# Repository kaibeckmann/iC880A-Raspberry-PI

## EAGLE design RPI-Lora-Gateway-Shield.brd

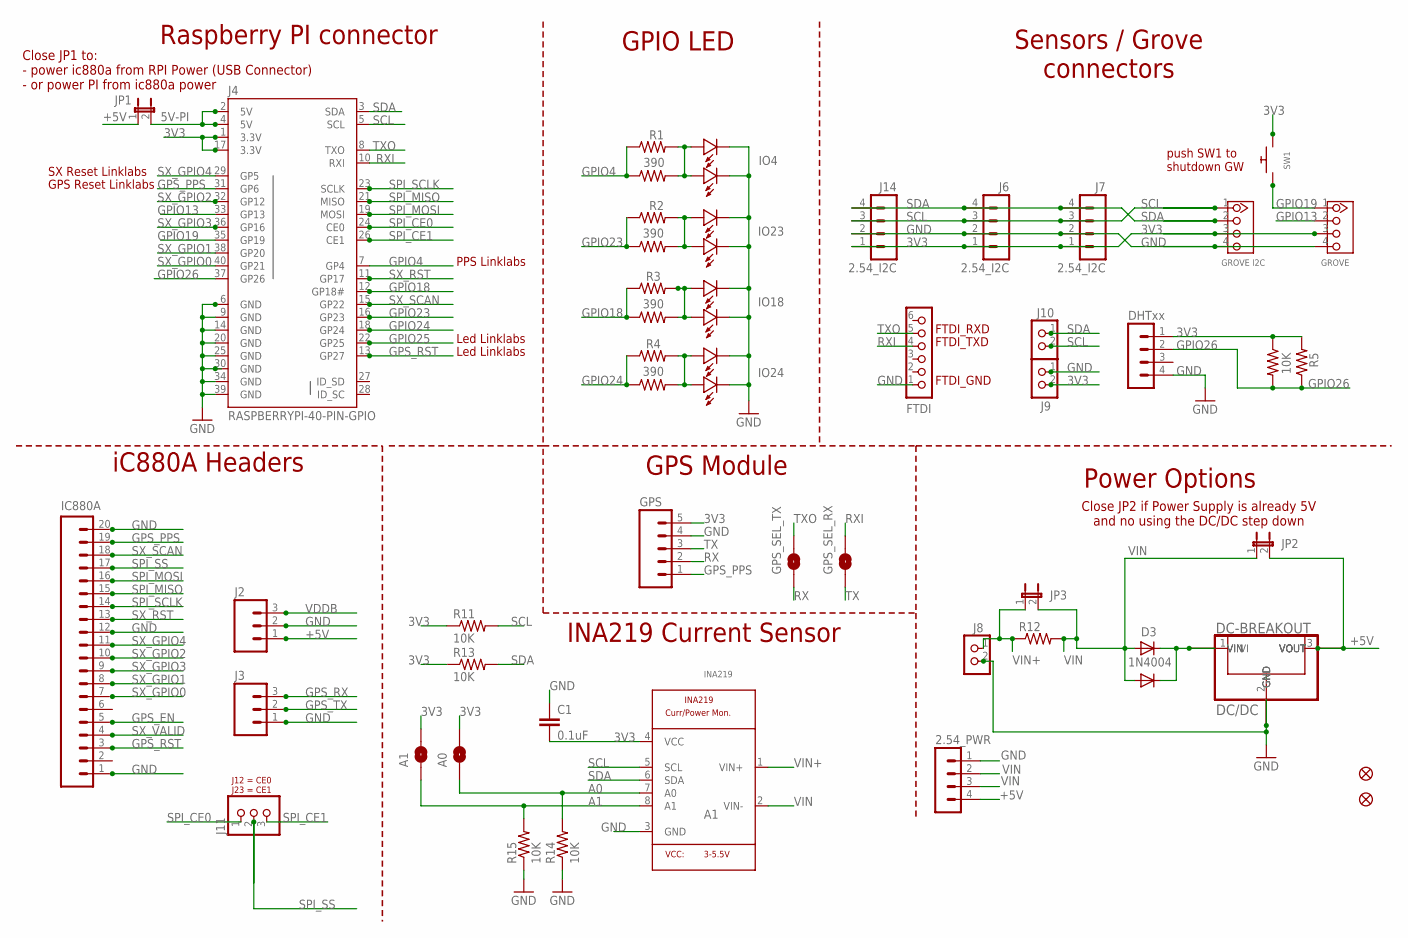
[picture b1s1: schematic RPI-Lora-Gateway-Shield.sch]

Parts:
A0, A1: SOLDERJUMPERNO; SJ_2S-NO
C1: 0.1uF; 0805-CAP
D3: 1N4004; DO41-10
D4: 1N4007; DO-214AC
DC/DC: DC-BREAKOUT
FID2, FID3: FIDUCIAL""; FIDUCIAL_1MM
FTDI: CON_HEADER_1X06-PTH; M1X6
GPS: M05PTH; 1X05
GPS_SEL_RX: SOLDERJUMPERNO; SJ_2S-NO
GPS_SEL_TX: SOLDERJUMPERNO; SJ_2S-NO
IC880A: M20LOCK; 1X20_LOCK
INA219: INA219; SOT23-8
J1: GROVE; HW4-2.0
J2, J3: M03LOCK; 1X03_LOCK
J4: RASPBERRYPI-40-PIN-GPIO; 2X20-SHROUDED
J5: DHTxx; 1X04_NO_LOCK
J6, J7, J14: 2.54_I2C; 1X04_NO_LOCK
J8, J9, J10: CON_TERMINAL_BLOCK_02-5MM; TERMINAL_BLOCK_2P_5
J11: JUMPER_1X30805; JP3_0805
J12: 2.54_PWR; 1X04_NO_LOCK
J13: GROVE I2C; HW4-2.0
JP1, JP2, JP3: JUMPER2
LED1, LED2, LED3, LED4: LED0805; 0805-LED
R1, R2, R3, R4: 390; AXIAL-0.4
R5: 10K; AXIAL-0.4
R6, R7, R8, R9, R10: RESISTOR0805-RES; 0805-RES
R11, R13, R14, R15: 10K; 0805
R12: R-US_R2512; R2512
SW1: SWITCH_PUSHBUTTONEVQ-PE; TACT_PANA-EVQ
U$4: IO4; LED3MM
U$5: IO23; LED3MM
U$6: IO18; LED3MM
U$7: IO24; LED3MM
U$8: DC-BREAKOUTFIXED; DC-DC-FIXED
U$11: OKI-78SR; OKI-78SRH

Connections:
3V3: A0.2, A1.2, C1.2, GPS.5, INA219.4 (VCC), J1.3, J4.1 (3.3V), J4.17 (3.3V), J5.1, J6.1, J7.1, J9.2, J13.3, J14.1, R5.P$1 (1), R10.2, R11.1, R13.1, SW1.P$2
5V-PI: J4.2 (5V), J4.4 (5V), JP1.2
+5V: DC/DC.VOUT-1 (VOUT), DC/DC.VOUT-2 (VOUT), J2.1, J12.4, JP1.1, JP2.2, U$8.VOUT-1 (VOUT), U$8.VOUT-2 (VOUT), U$11.3 (VO)
A0: A0.1, INA219.7 (A0), R14.2
A1: A1.1, INA219.8 (A1), R15.2
GND: C1.1, DC/DC.GND-1 (GND), DC/DC.GND-2 (GND), DC/DC.GND-3 (GND), DC/DC.GND-4 (GND), FTDI.1, GPS.4, IC880A.1, IC880A.12, IC880A.20, INA219.3 (GND), J1.4, J2.2, J3.1, J4.6 (GND), J4.9 (GND), J4.14 (GND), J4.20 (GND), J4.25 (GND), J4.30 (GND), J4.34 (GND), J4.39 (GND), J5.4, J6.2, J7.2, J8.2, J9.1, J12.1, J13.4, J14.2, LED1.MINUS, LED2.MINUS, LED3.MINUS, LED4.MINUS, R14.1, R15.1, U$4.MINUS, U$5.MINUS, U$6.MINUS, U$7.MINUS, U$8.GND-1 (GND), U$8.GND-2 (GND), U$8.GND-3 (GND), U$8.GND-4 (GND), U$11.2 (GND)
GPIO4: J4.7 (GP4), R1.P$1 (1), R6.1
GPIO13: J1.2, J4.33 (GP13)
GPIO18: J4.12 (GP18#), R3.P$1 (1), R8.1
GPIO19: J1.1, J4.35 (GP19), SW1.P$1
GPIO23: J4.16 (GP23), R2.P$1 (1), R7.1
GPIO24: J4.18 (GP24), R4.P$1 (1), R9.1
GPIO25: J4.22 (GP25)
GPIO26: J4.37 (GP26), J5.2, R5.P$2 (2), R10.1
GPS_EN: IC880A.5
GPS_PPS: GPS.1, IC880A.19, J4.31 (GP6)
GPS_RST: IC880A.3, J4.13 (GP27)
GPS_RX: J3.3
GPS_TX: J3.2
unnamed: D3.C, D4.1 (C), DC/DC.VIN-1 (VIN), DC/DC.VIN-2 (VIN), U$8.VIN-1 (VIN), U$8.VIN-2 (VIN), U$11.1 (VI)
unnamed: LED4.PLUS, R4.P$2 (2), R9.2, U$7.PLUS
unnamed: LED1.PLUS, R1.P$2 (2), R6.2, U$4.PLUS
unnamed: LED2.PLUS, R2.P$2 (2), R7.2, U$5.PLUS
unnamed: LED3.PLUS, R3.P$2 (2), R8.2, U$6.PLUS
RX: GPS.2, GPS_SEL_TX.1
RXI: FTDI.4, GPS_SEL_RX.2, J4.10 (RXI)
SCL: INA219.5 (SCL), J4.5 (SCL), J6.3, J7.3, J10.2, J13.1, J14.3, R11.2
SDA: INA219.6 (SDA), J4.3 (SDA), J6.4, J7.4, J10.1, J13.2, J14.4, R13.2
SPI_CE0: J4.24 (CE0), J11.1
SPI_CE1: J4.26 (CE1), J11.3
SPI_MISO: IC880A.15, J4.21 (MISO)
SPI_MOSI: IC880A.16, J4.19 (MOSI)
SPI_SCLK: IC880A.14, J4.23 (SCLK)
SPI_SS: IC880A.17, J11.2
SX_GPIO0: IC880A.7, J4.40 (GP21)
SX_GPIO1: IC880A.8, J4.38 (GP20)
SX_GPIO2: IC880A.10, J4.32 (GP12)
SX_GPIO3: IC880A.9, J4.36 (GP16)
SX_GPIO4: IC880A.11, J4.29 (GP5)
SX_RST: IC880A.13, J4.11 (GP17)
SX_SCAN: IC880A.18, J4.15 (GP22)
SX_VALID: IC880A.4
TX: GPS.3, GPS_SEL_RX.1
TXO: FTDI.5, GPS_SEL_TX.2, J4.8 (TXO)
VDDB: J2.3
VIN: D3.A, D4.2 (A), INA219.2 (VIN-), J12.2, J12.3, JP2.1, JP3.2, R12.2
VIN+: INA219.1 (VIN+), J8.1, JP3.1, R12.1

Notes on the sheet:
PPS Linklabs
SX Reset Linklabs
GPS Reset Linklabs
Led Linklabs
iC880A Headers
Power Options
Raspberry PI connector
GPIO LED
Sensors / Grove connectors
Close JP2 if Power Supply is already 5V and no using the DC/DC step down
Close JP1 to: - power ic880a from RPI Power (USB Connector) - or power PI from ic880a power
FTDI_RXD
FTDI_TXD
FTDI_GND
push SW1 to shutdown GW
GPS Module
INA219 Current Sensor

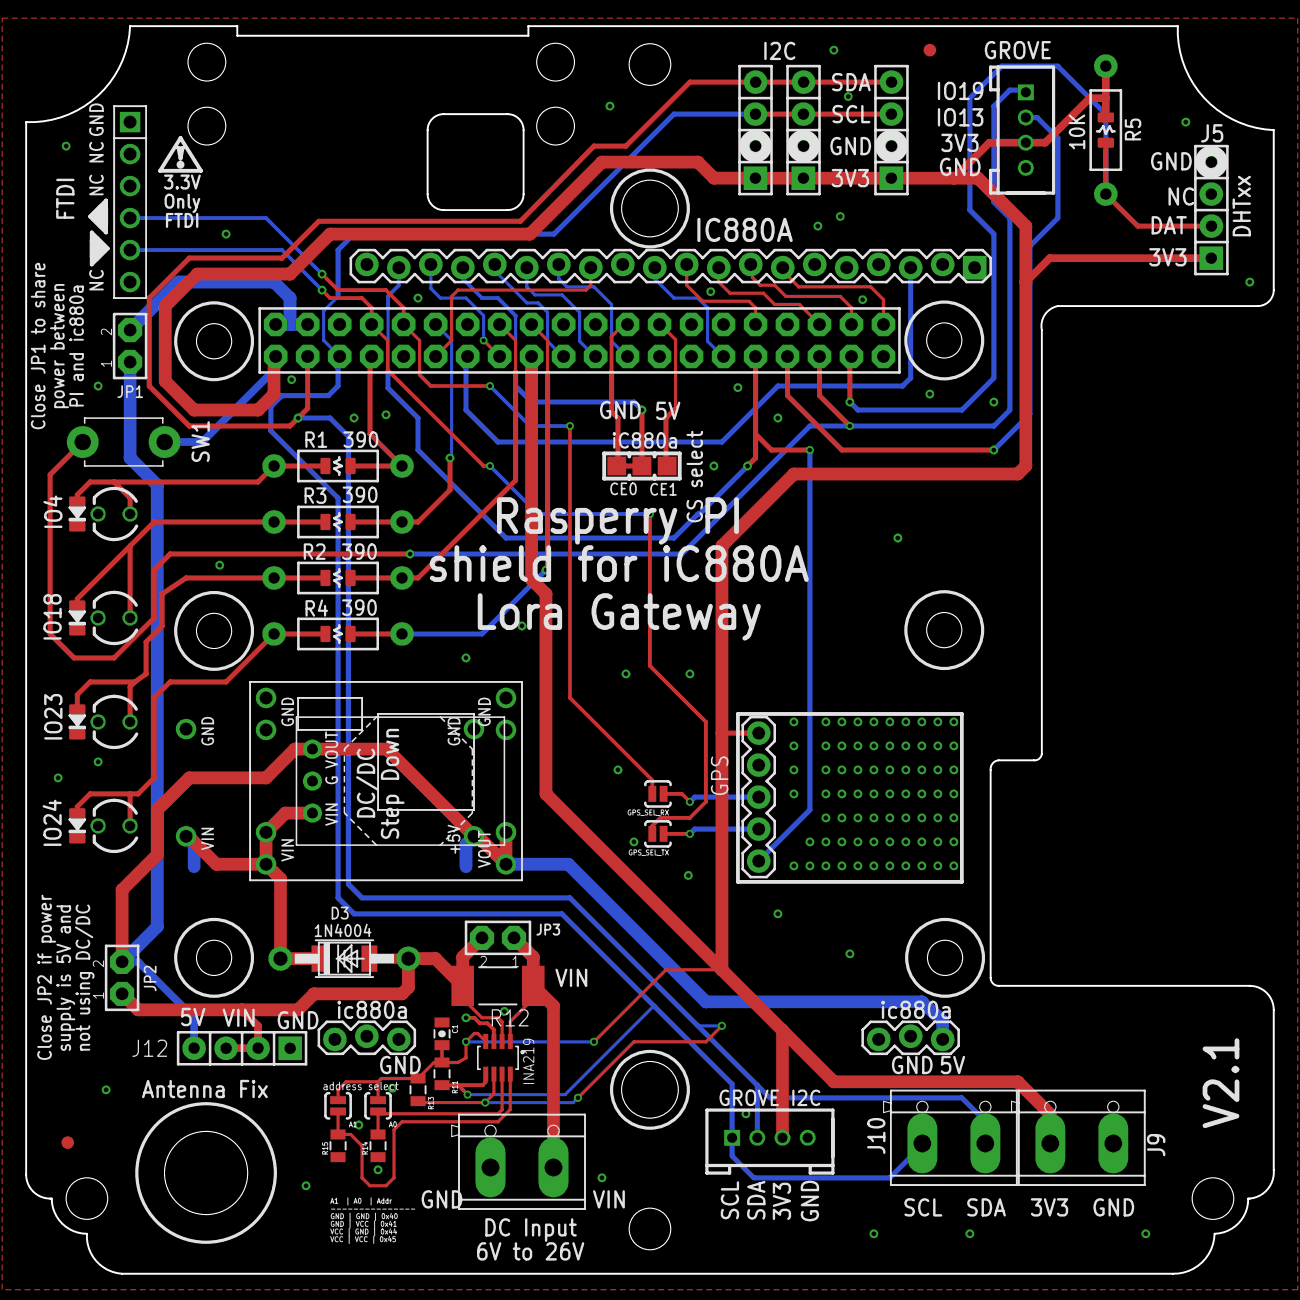
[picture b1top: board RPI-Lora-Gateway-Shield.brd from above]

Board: 2 copper layers, 99.1 x 99.1 mm, 61 parts (1 on the bottom side), 41 nets.

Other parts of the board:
H1, H2, H3, H4: STAND-OFF

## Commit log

2018-12-15 removed RFM9x, added GPS Module + INA219 current sensor
2018-12-16 added header for volt meter + holes for rasppi zero

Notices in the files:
parts and their libraries:
microbuilder: This work is placed in the public domain, and may be freely used for commercial and non-commercial work with the following conditions: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
SparkFun-Connectors: Licensing: Creative Commons ShareAlike 4.0 International - https://creativecommons.org/licenses/by-sa/4.0
